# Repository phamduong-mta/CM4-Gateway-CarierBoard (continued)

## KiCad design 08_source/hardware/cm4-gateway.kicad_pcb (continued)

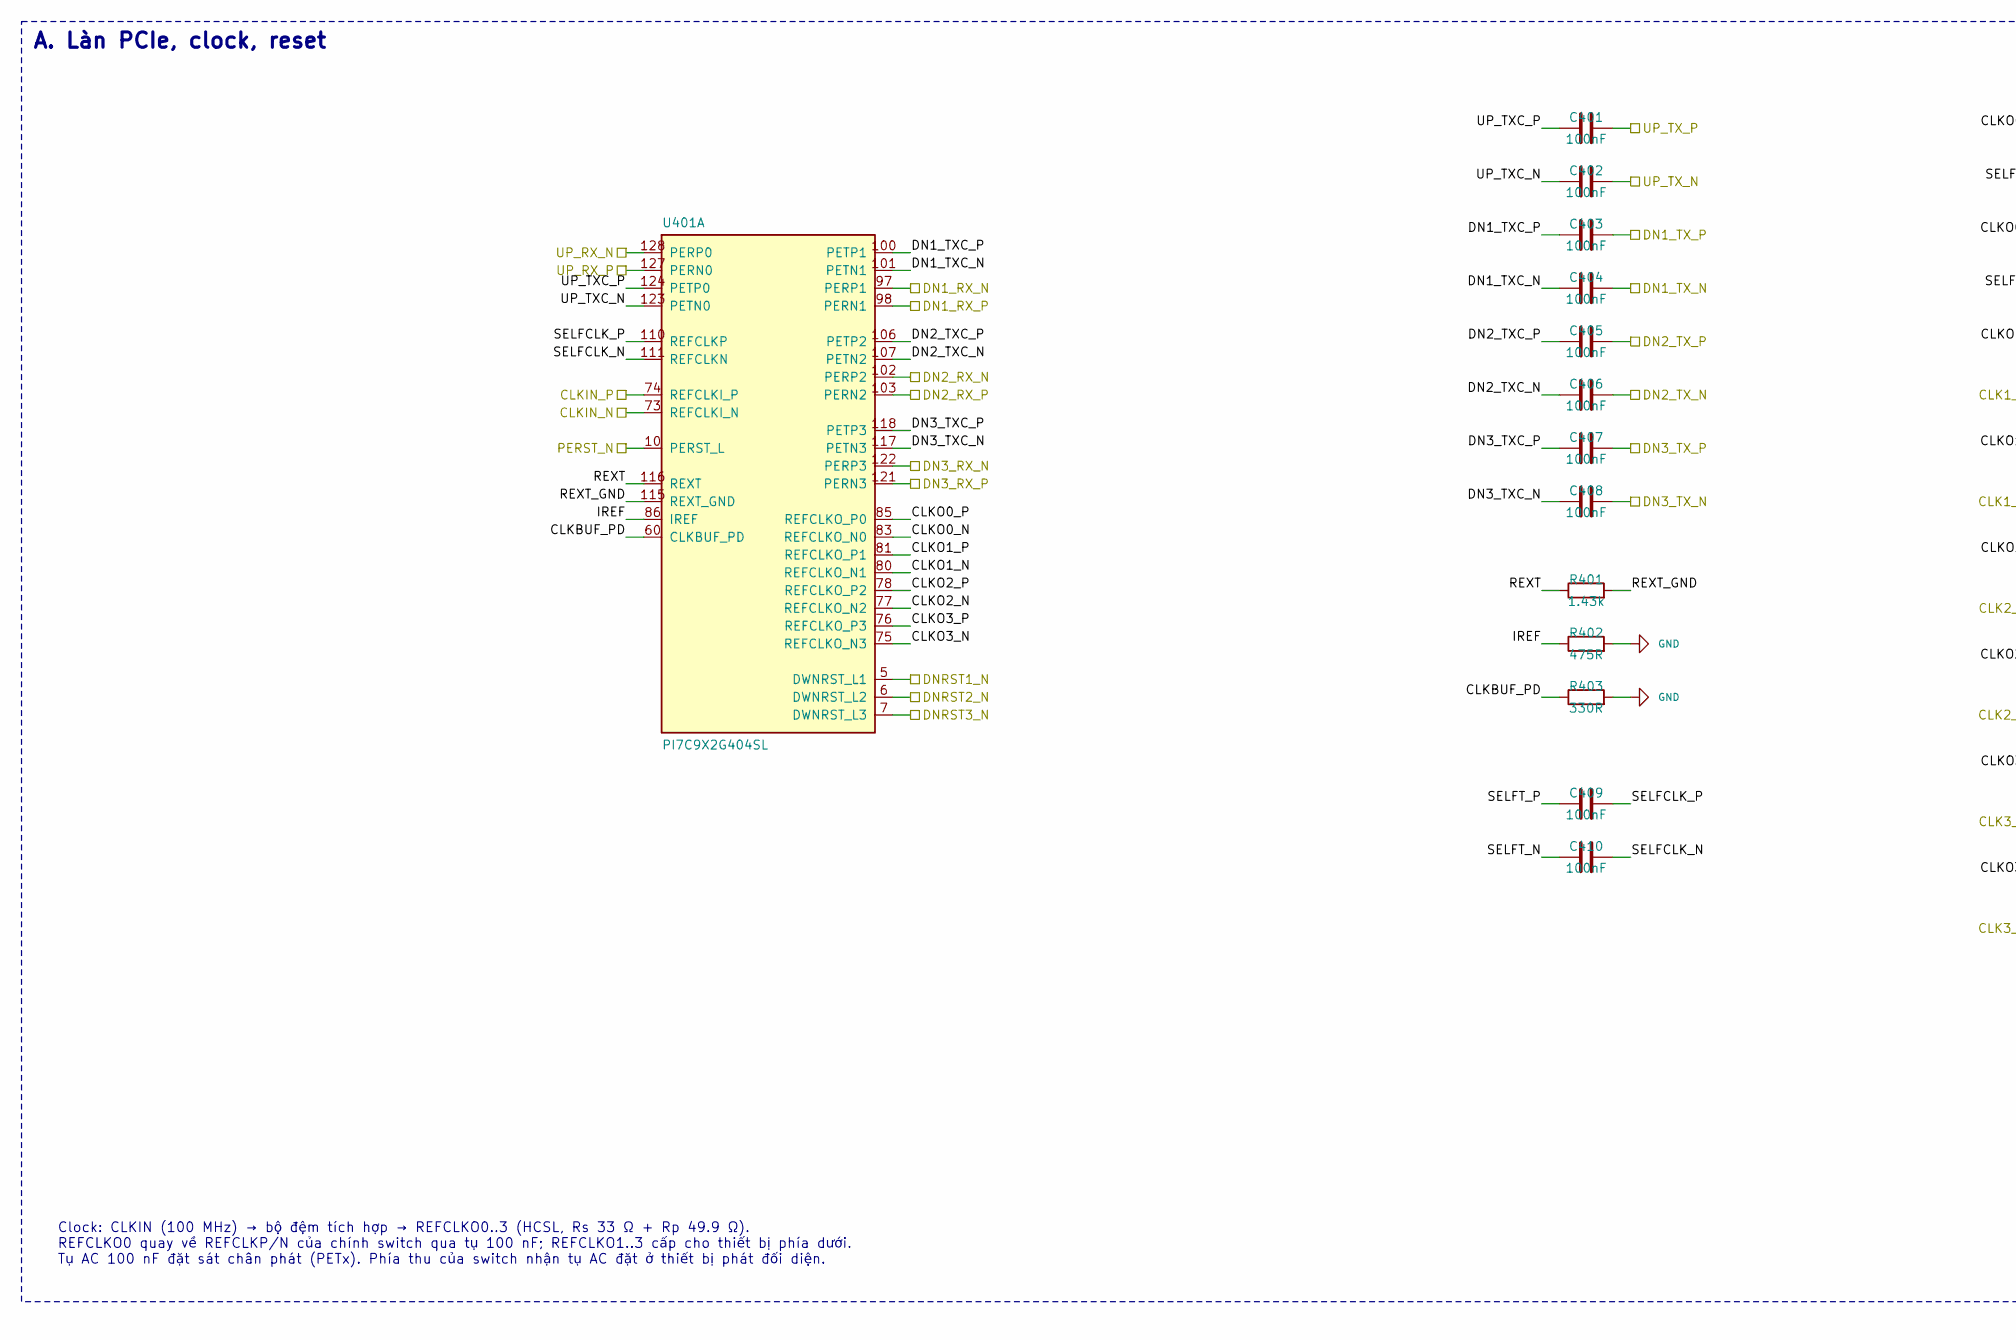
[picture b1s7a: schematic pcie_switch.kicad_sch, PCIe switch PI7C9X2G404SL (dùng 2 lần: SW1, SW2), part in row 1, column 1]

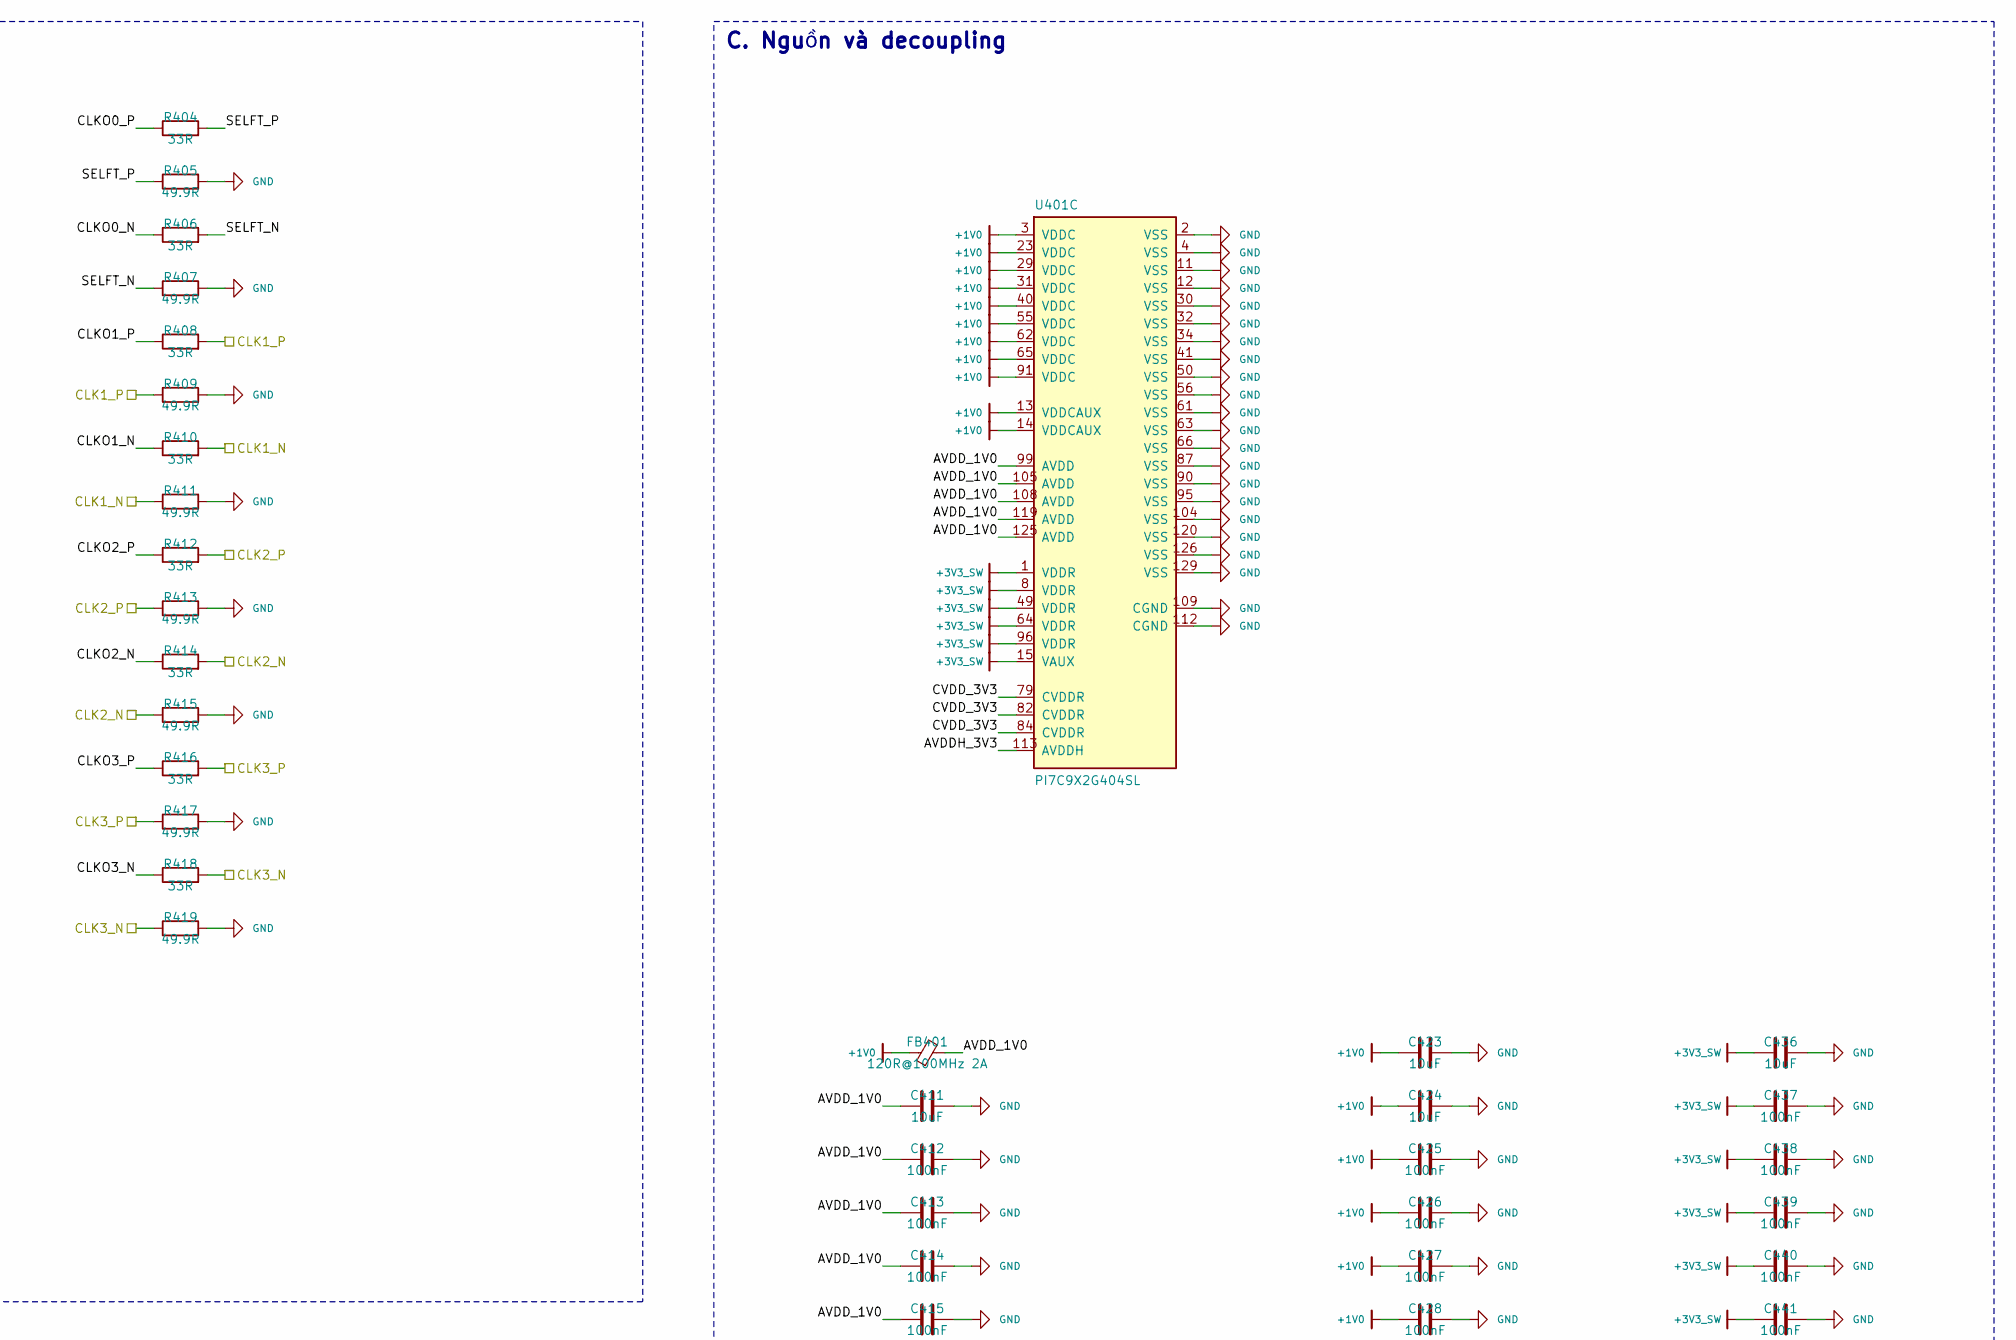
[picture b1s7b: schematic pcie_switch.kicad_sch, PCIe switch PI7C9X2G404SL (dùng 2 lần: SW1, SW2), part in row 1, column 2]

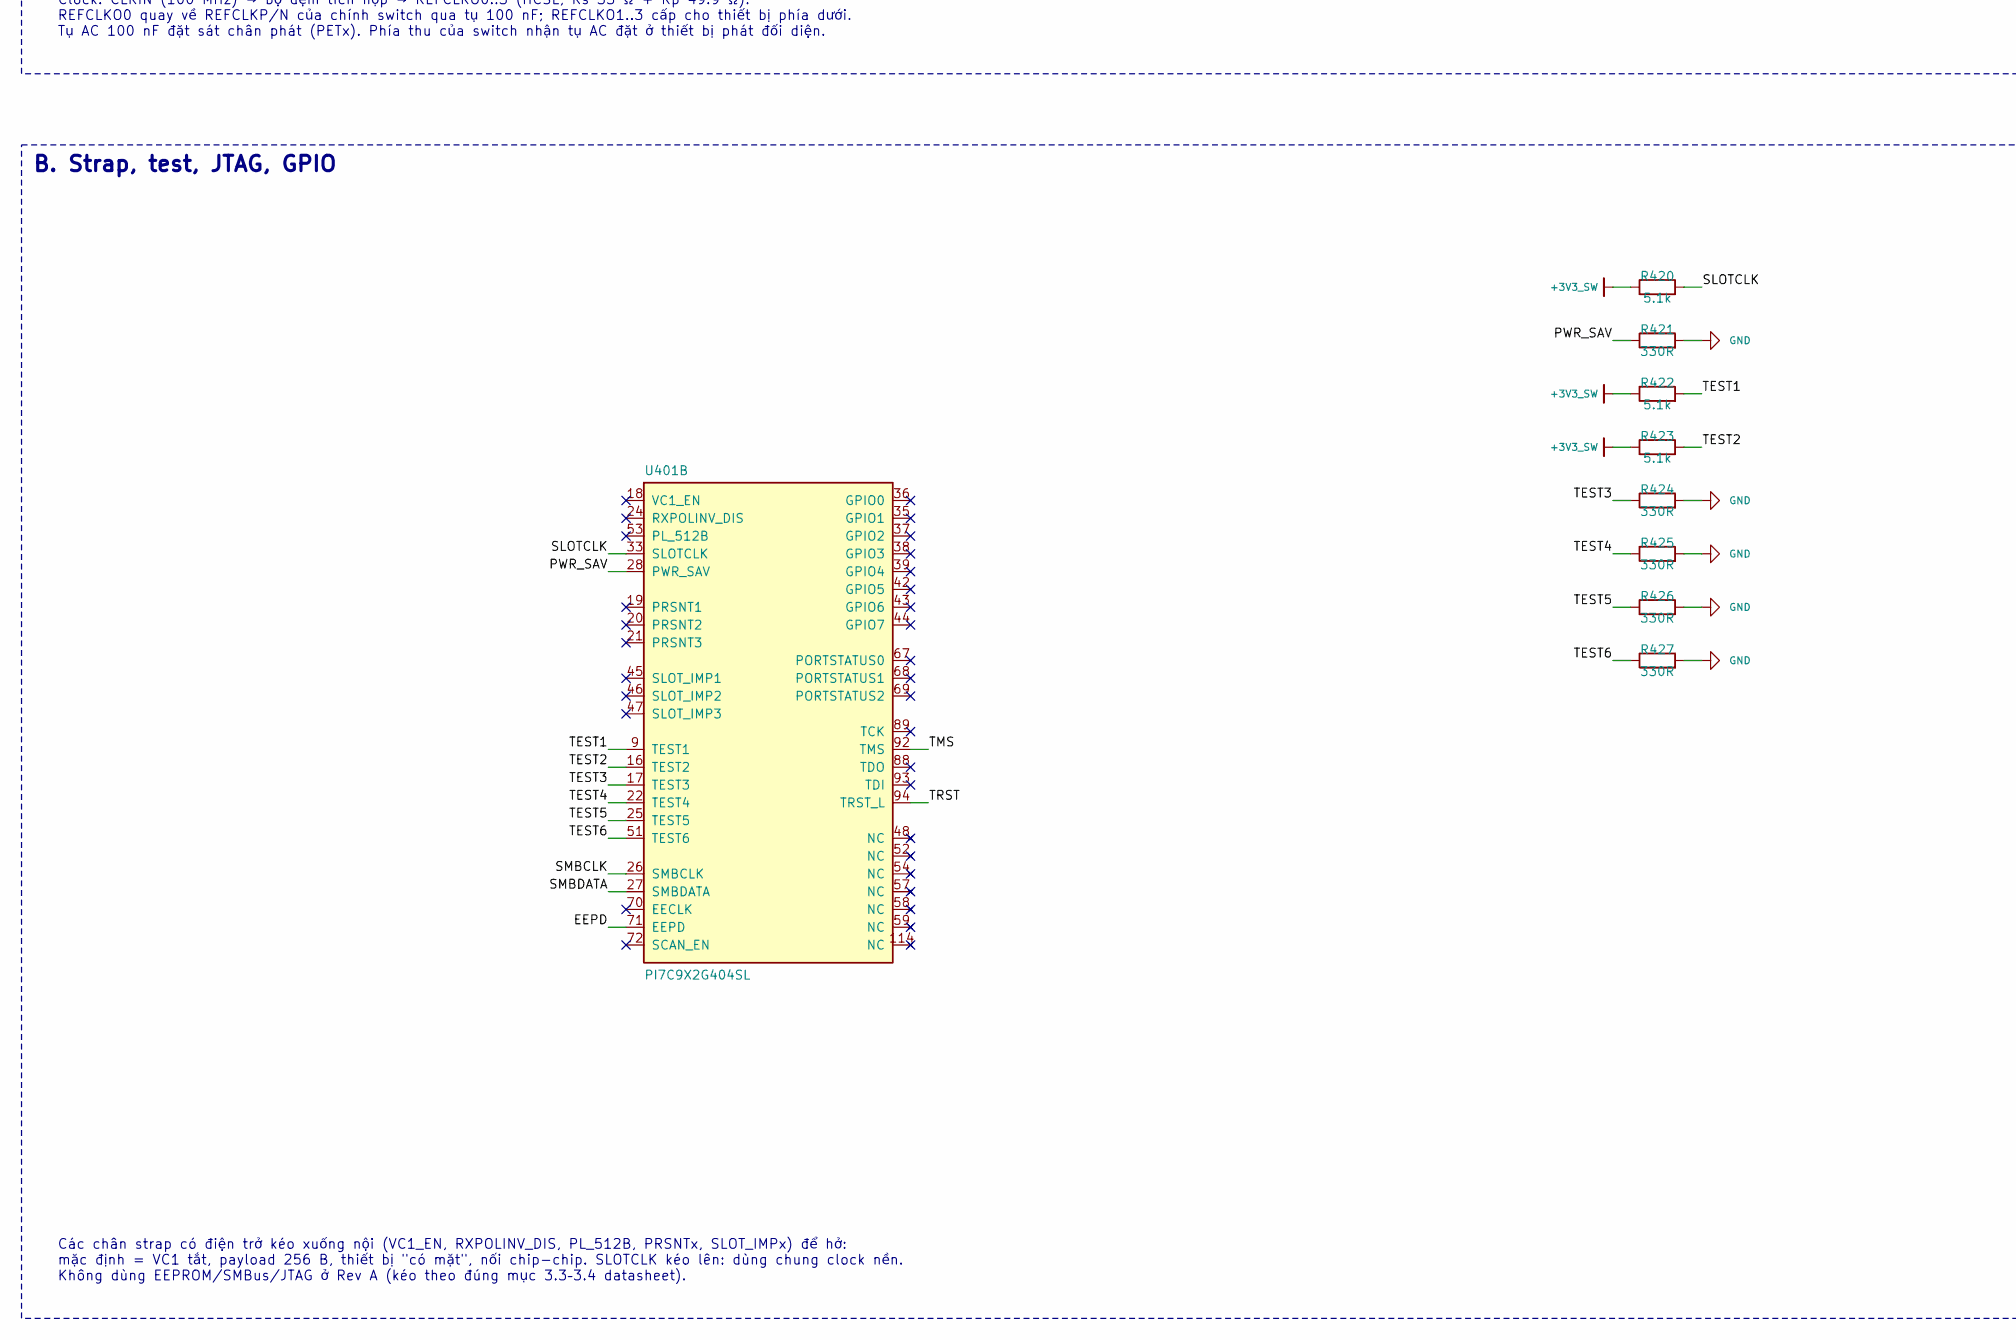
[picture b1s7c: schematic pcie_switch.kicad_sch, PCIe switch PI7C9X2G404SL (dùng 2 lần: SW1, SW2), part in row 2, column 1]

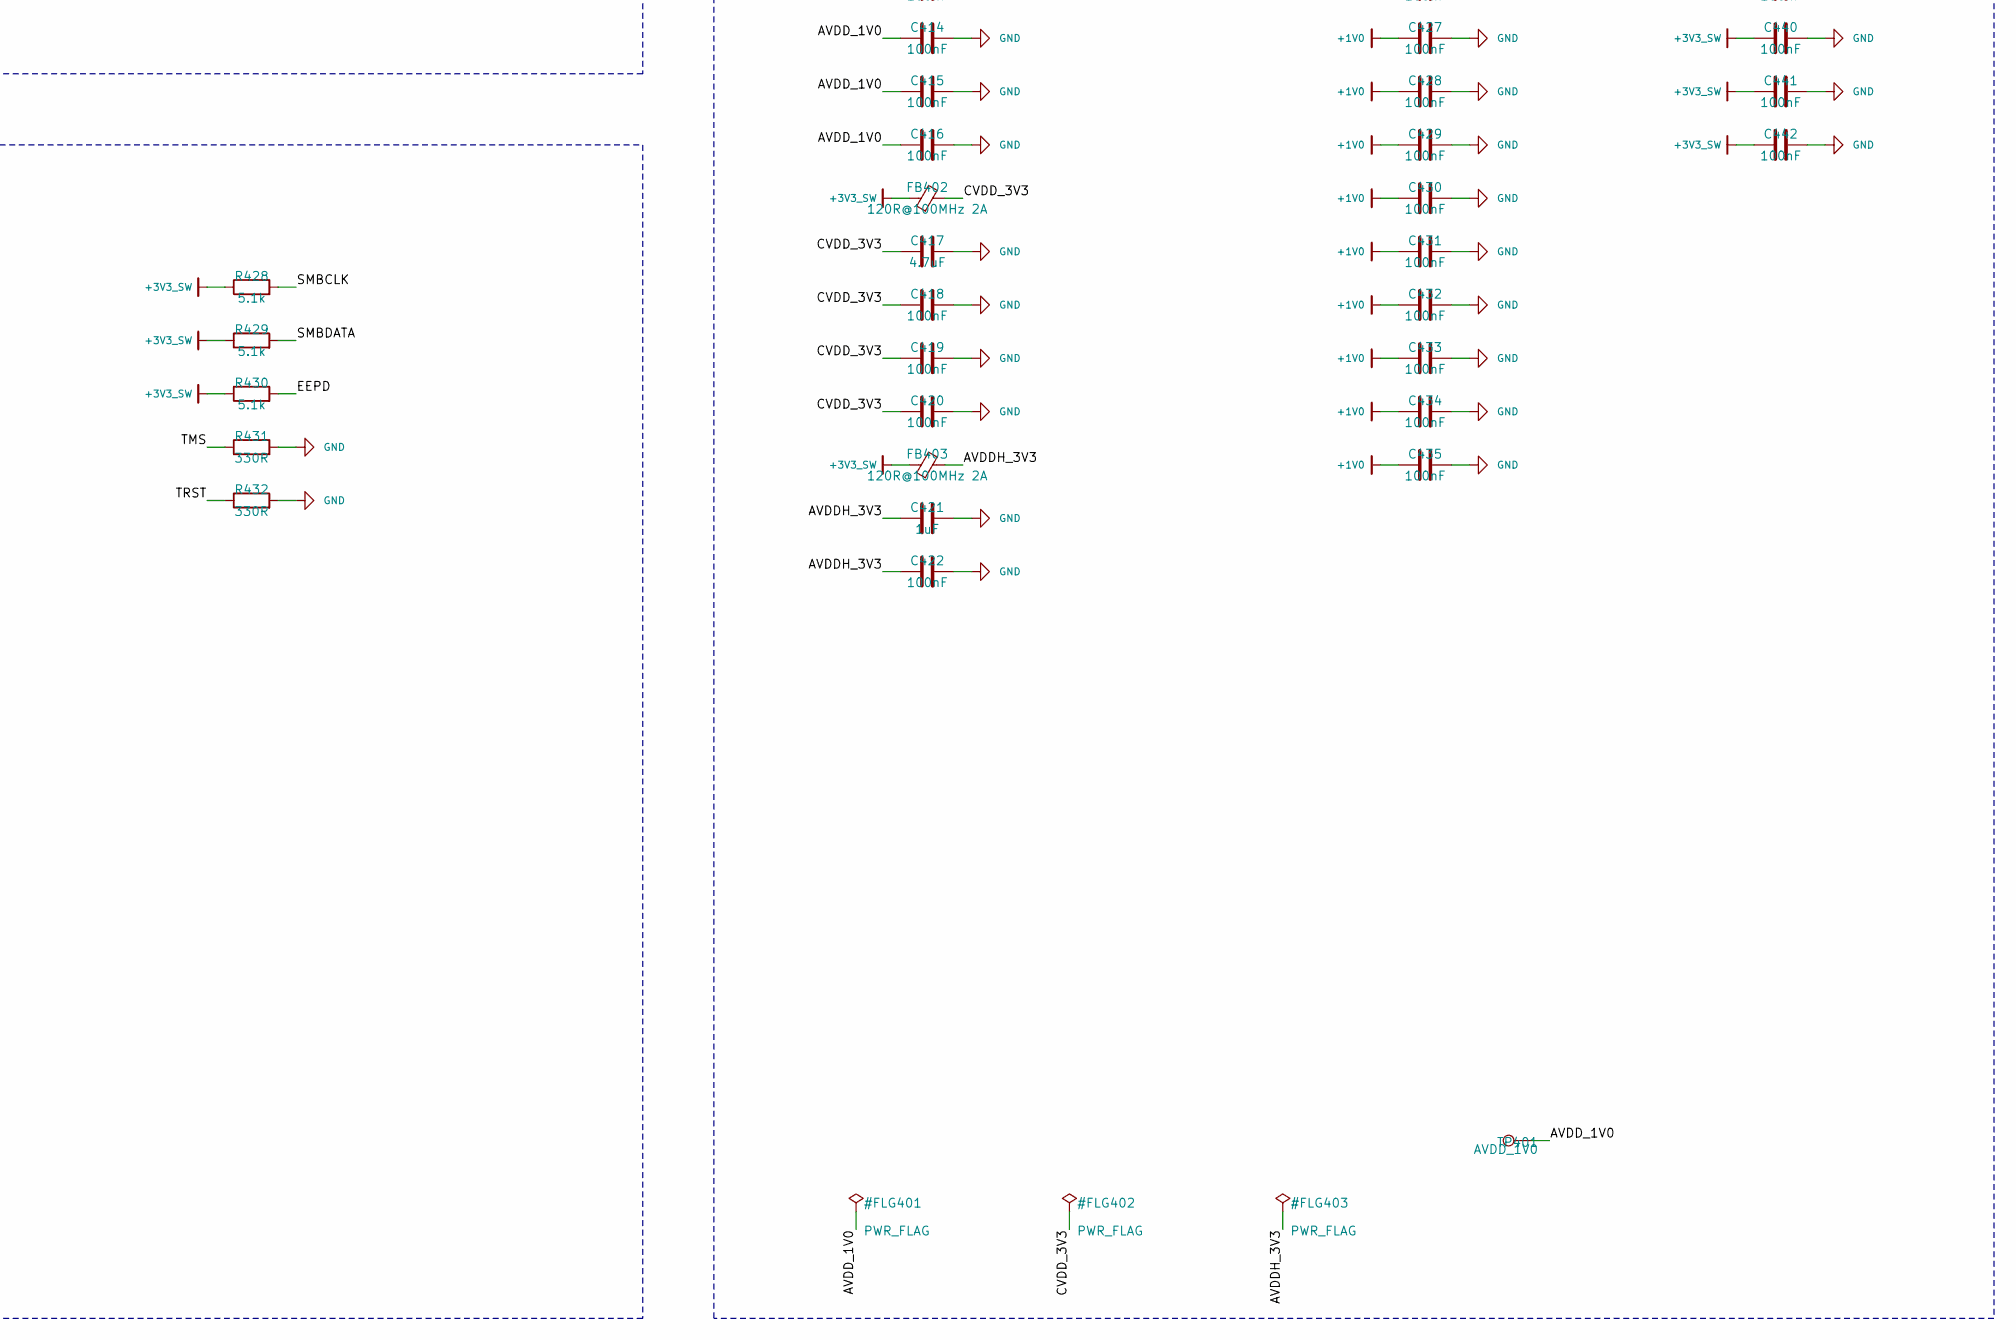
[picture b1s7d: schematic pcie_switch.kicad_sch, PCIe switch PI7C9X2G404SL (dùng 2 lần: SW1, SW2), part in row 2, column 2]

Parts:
C401, C402, C403, C404, C405, C406, C407, C408, C409, C410, C412, C413, C414, C415, C416, C418, C419, C420, C422, C425, C426, C427, C428, C429, C430, C431, C432, C433, C434, C435, C437, C438, C439, C440, C441, C442: 100nF; C_0402_1005Metric; MPN CL05B104KO5NNNC; LCSC C1525
C411, C423, C424, C436: 10uF; C_0603_1608Metric; MPN CL10A106KP8NNNC; LCSC C19702
C417: 4.7uF; C_0603_1608Metric; MPN CL10A475KO8NNNC; LCSC C19666
C421: 1uF; C_0402_1005Metric; MPN CL05A105KA5NQNC; LCSC C52923
FB401, FB402, FB403: 120R@100MHz 2A; L_0603_1608Metric; MPN BLM18PG121SN1D; LCSC C14709
R401: 1.43k; R_0402_1005Metric; MPN 0402WGF1431TCE; LCSC C11671
R402: 475R; R_0402_1005Metric; MPN 0402WGF4750TCE; LCSC C49065
R403, R421, R424, R425, R426, R427, R431, R432: 330R; R_0402_1005Metric; MPN 0402WGF3300TCE; LCSC C25104
R404, R406, R408, R410, R412, R414, R416, R418: 33R; R_0402_1005Metric; MPN 0402WGF330JTCE; LCSC C25105
R405, R407, R409, R411, R413, R415, R417, R419: 49.9R; R_0402_1005Metric; MPN 0402WGF499JTCE; LCSC C25120
R420, R422, R423, R428, R429, R430: 5.1k; R_0402_1005Metric; MPN 0402WGF5101TCE; LCSC C25905
TP401: AVDD_1V0; TestPoint_Pad_D1.0mm
U401: PI7C9X2G404SL; LQFP-128-1EP_14x14mm_P0.4mm_EP5.5x5.5mm; MPN PI7C9X2G404SLBFDEX; LCSC C500767

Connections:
+1V0: C423.1, C424.1, C425.1, C426.1, C427.1, C428.1, C429.1, C430.1, C431.1, C432.1, C433.1, C434.1, C435.1, FB401.1, U401.3 (VDDC), U401.13 (VDDCAUX), U401.14 (VDDCAUX), U401.23 (VDDC), U401.29 (VDDC), U401.31 (VDDC), U401.40 (VDDC), U401.55 (VDDC), U401.62 (VDDC), U401.65 (VDDC), U401.91 (VDDC); also elsewhere on the board
+3V3_SW: C436.1, C437.1, C438.1, C439.1, C440.1, C441.1, C442.1, FB402.1, FB403.1, R420.1, R422.1, R423.1, R428.1, R429.1, R430.1, U401.1 (VDDR), U401.8 (VDDR), U401.15 (VAUX), U401.49 (VDDR), U401.64 (VDDR), U401.96 (VDDR); also elsewhere on the board
/SW1/AVDDH_3V3: C421.1, C422.1, FB403.2, U401.113 (AVDDH)
/SW1/AVDD_1V0: C411.1, C412.1, C413.1, C414.1, C415.1, C416.1, FB401.2, TP401.1, U401.99 (AVDD), U401.105 (AVDD), U401.108 (AVDD), U401.119 (AVDD), U401.125 (AVDD)
/SW1/CLKBUF_PD: R403.1, U401.60 (CLKBUF_PD)
/SW1/CLKO0_N: R406.1, U401.83 (REFCLKO_N0)
/SW1/CLKO0_P: R404.1, U401.85 (REFCLKO_P0)
/SW1/CLKO1_N: R410.1, U401.80 (REFCLKO_N1)
/SW1/CLKO1_P: R408.1, U401.81 (REFCLKO_P1)
/SW1/CLKO2_N: R414.1, U401.77 (REFCLKO_N2)
/SW1/CLKO2_P: R412.1, U401.78 (REFCLKO_P2)
/SW1/CLKO3_N: R418.1, U401.75 (REFCLKO_N3)
/SW1/CLKO3_P: R416.1, U401.76 (REFCLKO_P3)
/SW1/CVDD_3V3: C417.1, C418.1, C419.1, C420.1, FB402.2, U401.79 (CVDDR), U401.82 (CVDDR), U401.84 (CVDDR)
/SW1/DN1_TXC_N: C404.1, U401.101 (PETN1)
/SW1/DN1_TXC_P: C403.1, U401.100 (PETP1)
/SW1/DN2_TXC_N: C406.1, U401.107 (PETN2)
/SW1/DN2_TXC_P: C405.1, U401.106 (PETP2)
/SW1/DN3_TXC_N: C408.1, U401.117 (PETN3)
/SW1/DN3_TXC_P: C407.1, U401.118 (PETP3)
/SW1/EEPD: R430.2, U401.71 (EEPD)
/SW1/IREF: R402.1, U401.86 (IREF)
/SW1/PWR_SAV: R421.1, U401.28 (PWR_SAV)
/SW1/REXT: R401.1, U401.116 (REXT)
/SW1/REXT_GND: R401.2, U401.115 (REXT_GND)
/SW1/SELFCLK_N: C410.2, U401.111 (REFCLKN)
/SW1/SELFCLK_P: C409.2, U401.110 (REFCLKP)
/SW1/SELFT_N: C410.1, R406.2, R407.1
/SW1/SELFT_P: C409.1, R404.2, R405.1
/SW1/SLOTCLK: R420.2, U401.33 (SLOTCLK)
/SW1/SMBCLK: R428.2, U401.26 (SMBCLK)
/SW1/SMBDATA: R429.2, U401.27 (SMBDATA)
/SW1/TEST1: R422.2, U401.9 (TEST1)
/SW1/TEST2: R423.2, U401.16 (TEST2)
/SW1/TEST3: R424.1, U401.17 (TEST3)
/SW1/TEST4: R425.1, U401.22 (TEST4)
/SW1/TEST5: R426.1, U401.25 (TEST5)
/SW1/TEST6: R427.1, U401.51 (TEST6)
/SW1/TMS: R431.1, U401.92 (TMS)
/SW1/TRST: R432.1, U401.94 (TRST_L)
/SW1/UP_TXC_N: C402.1, U401.123 (PETN0)
/SW1/UP_TXC_P: C401.1, U401.124 (PETP0)
GND: C411.2, C412.2, C413.2, C414.2, C415.2, C416.2, C417.2, C418.2, C419.2, C420.2, C421.2, C422.2, C423.2, C424.2, C425.2, C426.2, C427.2, C428.2, C429.2, C430.2, C431.2, C432.2, C433.2, C434.2, C435.2, C436.2, C437.2, C438.2, C439.2, C440.2, C441.2, C442.2, R402.2, R403.2, R405.2, R407.2, R409.2, R411.2, R413.2, R415.2, R417.2, R419.2, R421.2, R424.2, R425.2, R426.2, R427.2, R431.2, R432.2, U401.2 (VSS), U401.4 (VSS), U401.11 (VSS), U401.12 (VSS), U401.30 (VSS), U401.32 (VSS), U401.34 (VSS), U401.41 (VSS), U401.50 (VSS), U401.56 (VSS), U401.61 (VSS), U401.63 (VSS), U401.66 (VSS), U401.87 (VSS), U401.90 (VSS), U401.95 (VSS), U401.104 (VSS), U401.109 (CGND), U401.112 (CGND), U401.120 (VSS), U401.126 (VSS), U401.129 (VSS); also elsewhere on the board
P1_CLK_N: R410.2, R411.1; also elsewhere on the board
P1_CLK_P: R408.2, R409.1; also elsewhere on the board
P1_NIC2SW_N: U401.102 (PERP2); also elsewhere on the board
P1_NIC2SW_P: U401.103 (PERN2); also elsewhere on the board
P1_RST_N: U401.6 (DWNRST_L2); also elsewhere on the board
P1_SW2NIC_N: C406.2; also elsewhere on the board
P1_SW2NIC_P: C405.2; also elsewhere on the board
P2_CLK_N: R414.2, R415.1; also elsewhere on the board
P2_CLK_P: R412.2, R413.1; also elsewhere on the board
P2_NIC2SW_N: U401.97 (PERP1); also elsewhere on the board
P2_NIC2SW_P: U401.98 (PERN1); also elsewhere on the board
P2_RST_N: U401.5 (DWNRST_L1); also elsewhere on the board
P2_SW2NIC_N: C404.2; also elsewhere on the board
P2_SW2NIC_P: C403.2; also elsewhere on the board
PCIE_CLK_N: U401.73 (REFCLKI_N); also elsewhere on the board
PCIE_CLK_P: U401.74 (REFCLKI_P); also elsewhere on the board
PCIE_RST_N: U401.10 (PERST_L); also elsewhere on the board
PCIE_RX_N: C402.2; also elsewhere on the board
PCIE_RX_P: C401.2; also elsewhere on the board
PCIE_TX_N: U401.128 (PERP0); also elsewhere on the board
PCIE_TX_P: U401.127 (PERN0); also elsewhere on the board
SW2_CLK_N: R418.2, R419.1; also elsewhere on the board
SW2_CLK_P: R416.2, R417.1; also elsewhere on the board
SW2_RST_N: U401.7 (DWNRST_L3); also elsewhere on the board
X_SW1TO2_N: C408.2; also elsewhere on the board
X_SW1TO2_P: C407.2; also elsewhere on the board
X_SW2TO1_N: U401.122 (PERP3); also elsewhere on the board
X_SW2TO1_P: U401.121 (PERN3); also elsewhere on the board

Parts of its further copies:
C501, C502, C503, C504, C505, C506, C507, C508, C509, C510, C512, C513, C514, C515, C516, C518, C519, C520, C522, C525, C526, C527, C528, C529, C530, C531, C532, C533, C534, C535, C537, C538, C539, C540, C541, C542: 100nF; C_0402_1005Metric; MPN CL05B104KO5NNNC; LCSC C1525
C511, C523, C524, C536: 10uF; C_0603_1608Metric; MPN CL10A106KP8NNNC; LCSC C19702
C517: 4.7uF; C_0603_1608Metric; MPN CL10A475KO8NNNC; LCSC C19666
C521: 1uF; C_0402_1005Metric; MPN CL05A105KA5NQNC; LCSC C52923
FB501, FB502, FB503: 120R@100MHz 2A; L_0603_1608Metric; MPN BLM18PG121SN1D; LCSC C14709
R501: 1.43k; R_0402_1005Metric; MPN 0402WGF1431TCE; LCSC C11671
R502: 475R; R_0402_1005Metric; MPN 0402WGF4750TCE; LCSC C49065
R503, R521, R524, R525, R526, R527, R531, R532: 330R; R_0402_1005Metric; MPN 0402WGF3300TCE; LCSC C25104
R504, R506, R508, R510, R512, R514, R516, R518: 33R; R_0402_1005Metric; MPN 0402WGF330JTCE; LCSC C25105
R505, R507, R509, R511, R513, R515, R517, R519: 49.9R; R_0402_1005Metric; MPN 0402WGF499JTCE; LCSC C25120
R520, R522, R523, R528, R529, R530: 5.1k; R_0402_1005Metric; MPN 0402WGF5101TCE; LCSC C25905
TP501: AVDD_1V0; TestPoint_Pad_D1.0mm
U501: PI7C9X2G404SL; LQFP-128-1EP_14x14mm_P0.4mm_EP5.5x5.5mm; MPN PI7C9X2G404SLBFDEX; LCSC C500767

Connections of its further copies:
+1V0: C523.1, C524.1, C525.1, C526.1, C527.1, C528.1, C529.1, C530.1, C531.1, C532.1, C533.1, C534.1, C535.1, FB501.1, U501.3 (VDDC), U501.13 (VDDCAUX), U501.14 (VDDCAUX), U501.23 (VDDC), U501.29 (VDDC), U501.31 (VDDC), U501.40 (VDDC), U501.55 (VDDC), U501.62 (VDDC), U501.65 (VDDC), U501.91 (VDDC); also elsewhere on the board
+3V3_SW: C536.1, C537.1, C538.1, C539.1, C540.1, C541.1, C542.1, FB502.1, FB503.1, R520.1, R522.1, R523.1, R528.1, R529.1, R530.1, U501.1 (VDDR), U501.8 (VDDR), U501.15 (VAUX), U501.49 (VDDR), U501.64 (VDDR), U501.96 (VDDR); also elsewhere on the board
/SW2/AVDDH_3V3: C521.1, C522.1, FB503.2, U501.113 (AVDDH)
/SW2/AVDD_1V0: C511.1, C512.1, C513.1, C514.1, C515.1, C516.1, FB501.2, TP501.1, U501.99 (AVDD), U501.105 (AVDD), U501.108 (AVDD), U501.119 (AVDD), U501.125 (AVDD)
/SW2/CLK3_N: R518.2, R519.1
/SW2/CLK3_P: R516.2, R517.1
/SW2/CLKBUF_PD: R503.1, U501.60 (CLKBUF_PD)
/SW2/CLKO0_N: R506.1, U501.83 (REFCLKO_N0)
/SW2/CLKO0_P: R504.1, U501.85 (REFCLKO_P0)
/SW2/CLKO1_N: R510.1, U501.80 (REFCLKO_N1)
/SW2/CLKO1_P: R508.1, U501.81 (REFCLKO_P1)
/SW2/CLKO2_N: R514.1, U501.77 (REFCLKO_N2)
/SW2/CLKO2_P: R512.1, U501.78 (REFCLKO_P2)
/SW2/CLKO3_N: R518.1, U501.75 (REFCLKO_N3)
/SW2/CLKO3_P: R516.1, U501.76 (REFCLKO_P3)
/SW2/CVDD_3V3: C517.1, C518.1, C519.1, C520.1, FB502.2, U501.79 (CVDDR), U501.82 (CVDDR), U501.84 (CVDDR)
/SW2/DN1_TXC_N: C504.1, U501.101 (PETN1)
/SW2/DN1_TXC_P: C503.1, U501.100 (PETP1)
/SW2/DN2_TXC_N: C506.1, U501.107 (PETN2)
/SW2/DN2_TXC_P: C505.1, U501.106 (PETP2)
/SW2/DN3_RX_N: U501.122 (PERP3)
/SW2/DN3_RX_P: U501.121 (PERN3)
/SW2/DN3_TXC_N: C508.1, U501.117 (PETN3)
/SW2/DN3_TXC_P: C507.1, U501.118 (PETP3)
/SW2/DN3_TX_N: C508.2
/SW2/DN3_TX_P: C507.2
/SW2/DNRST3_N: U501.7 (DWNRST_L3)
/SW2/EEPD: R530.2, U501.71 (EEPD)
/SW2/IREF: R502.1, U501.86 (IREF)
/SW2/PWR_SAV: R521.1, U501.28 (PWR_SAV)
/SW2/REXT: R501.1, U501.116 (REXT)
/SW2/REXT_GND: R501.2, U501.115 (REXT_GND)
/SW2/SELFCLK_N: C510.2, U501.111 (REFCLKN)
/SW2/SELFCLK_P: C509.2, U501.110 (REFCLKP)
/SW2/SELFT_N: C510.1, R506.2, R507.1
/SW2/SELFT_P: C509.1, R504.2, R505.1
/SW2/SLOTCLK: R520.2, U501.33 (SLOTCLK)
/SW2/SMBCLK: R528.2, U501.26 (SMBCLK)
/SW2/SMBDATA: R529.2, U501.27 (SMBDATA)
/SW2/TEST1: R522.2, U501.9 (TEST1)
/SW2/TEST2: R523.2, U501.16 (TEST2)
/SW2/TEST3: R524.1, U501.17 (TEST3)
/SW2/TEST4: R525.1, U501.22 (TEST4)
/SW2/TEST5: R526.1, U501.25 (TEST5)
/SW2/TEST6: R527.1, U501.51 (TEST6)
/SW2/TMS: R531.1, U501.92 (TMS)
/SW2/TRST: R532.1, U501.94 (TRST_L)
/SW2/UP_TXC_N: C502.1, U501.123 (PETN0)
/SW2/UP_TXC_P: C501.1, U501.124 (PETP0)
GND: C511.2, C512.2, C513.2, C514.2, C515.2, C516.2, C517.2, C518.2, C519.2, C520.2, C521.2, C522.2, C523.2, C524.2, C525.2, C526.2, C527.2, C528.2, C529.2, C530.2, C531.2, C532.2, C533.2, C534.2, C535.2, C536.2, C537.2, C538.2, C539.2, C540.2, C541.2, C542.2, R502.2, R503.2, R505.2, R507.2, R509.2, R511.2, R513.2, R515.2, R517.2, R519.2, R521.2, R524.2, R525.2, R526.2, R527.2, R531.2, R532.2, U501.2 (VSS), U501.4 (VSS), U501.11 (VSS), U501.12 (VSS), U501.30 (VSS), U501.32 (VSS), U501.34 (VSS), U501.41 (VSS), U501.50 (VSS), U501.56 (VSS), U501.61 (VSS), U501.63 (VSS), U501.66 (VSS), U501.87 (VSS), U501.90 (VSS), U501.95 (VSS), U501.104 (VSS), U501.109 (CGND), U501.112 (CGND), U501.120 (VSS), U501.126 (VSS), U501.129 (VSS); also elsewhere on the board
P3_CLK_N: R510.2, R511.1; also elsewhere on the board
P3_CLK_P: R508.2, R509.1; also elsewhere on the board
P3_NIC2SW_N: U501.102 (PERP2); also elsewhere on the board
P3_NIC2SW_P: U501.103 (PERN2); also elsewhere on the board
P3_RST_N: U501.6 (DWNRST_L2); also elsewhere on the board
P3_SW2NIC_N: C506.2; also elsewhere on the board
P3_SW2NIC_P: C505.2; also elsewhere on the board
P4_CLK_N: R514.2, R515.1; also elsewhere on the board
P4_CLK_P: R512.2, R513.1; also elsewhere on the board
P4_NIC2SW_N: U501.97 (PERP1); also elsewhere on the board
P4_NIC2SW_P: U501.98 (PERN1); also elsewhere on the board
P4_RST_N: U501.5 (DWNRST_L1); also elsewhere on the board
P4_SW2NIC_N: C504.2; also elsewhere on the board
P4_SW2NIC_P: C503.2; also elsewhere on the board
SW2_CLK_N: U501.73 (REFCLKI_N); also elsewhere on the board
SW2_CLK_P: U501.74 (REFCLKI_P); also elsewhere on the board
SW2_RST_N: U501.10 (PERST_L); also elsewhere on the board
X_SW1TO2_N: U501.128 (PERP0); also elsewhere on the board
X_SW1TO2_P: U501.127 (PERN0); also elsewhere on the board
X_SW2TO1_N: C502.2; also elsewhere on the board
X_SW2TO1_P: C501.2; also elsewhere on the board

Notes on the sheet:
A. Làn PCIe, clock, reset
Clock: CLKIN (100 MHz) → bộ đệm tích hợp → REFCLKO0..3 (HCSL, Rs 33 Ω + Rp 49.9 Ω). REFCLKO0 quay về REFCLKP/N của chính switch qua tụ 100 nF; REFCLKO1..3 cấp cho thiết bị phía dưới. Tụ AC 100 nF đặt sát chân phát (PETx). Phía thu của switch nhận tụ AC đặt ở thiết bị phát đối diện.
B. Strap, test, JTAG, GPIO
Các chân strap có điện trở kéo xuống nội (VC1_EN, RXPOLINV_DIS, PL_512B, PRSNTx, SLOT_IMPx) để hở: mặc định = VC1 tắt, payload 256 B, thiết bị "có mặt", nối chip-chip. SLOTCLK kéo lên: dùng chung clock nền. Không dùng EEPROM/SMBus/JTAG ở Rev A (kéo theo đúng mục 3.3–3.4 datasheet).
C. Nguồn và decoupling
